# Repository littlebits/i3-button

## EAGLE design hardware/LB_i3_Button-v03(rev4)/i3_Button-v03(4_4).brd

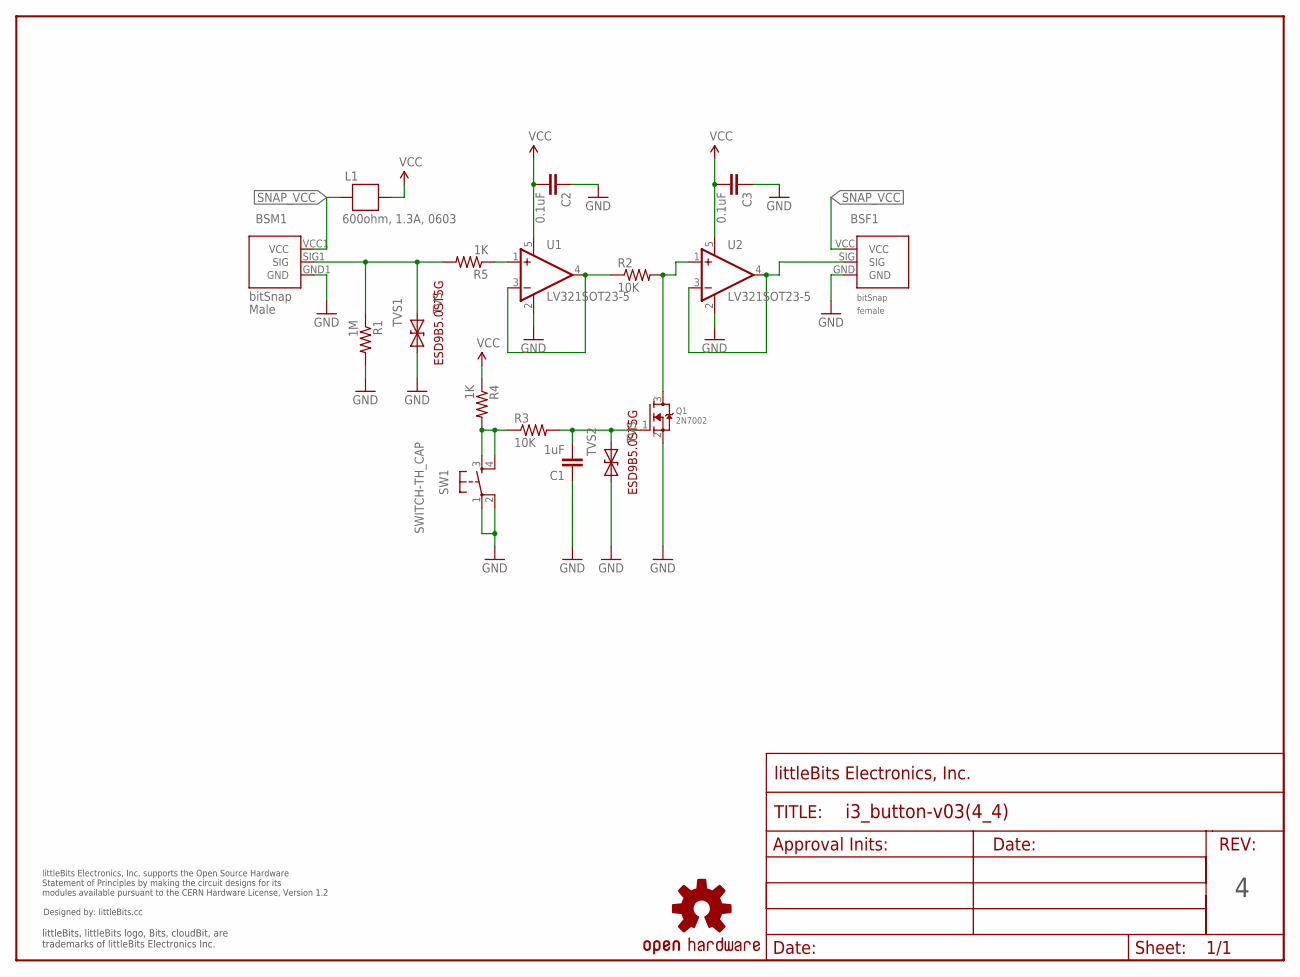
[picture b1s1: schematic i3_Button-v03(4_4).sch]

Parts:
BSF1: BITSNAP_V03_FEMALE
BSM1: BITSNAP_V03_MALE
C1: 1uF; 0603-CAP
C2, C3: 0.1uF; 0603-CAP
FRAME1: FRAME-LETTER-OHWOHW; FABDWG01-OHW
L1: 600ohm, 1.3A, 0603; R0603
Q1: 2N7002; SOT23
R1: 1M; 0603-RES
R2, R3: 10K; 0603-RES
R4, R5: 1K; 0603-RES
SW1: SWITCH-TH_CAP
TVS1, TVS2: TVS; SOD-923
U1, U2: LV321SOT23-5; SOT23-5
U$1: OSHW-LOGOL; OSHW-LOGO-L
U$2: OSHWCREDIT

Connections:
GND: BSF1.GND, BSM1.GND1 (GND), C1.1, C2.1, C3.1, Q1.2 (S), R1.2, SW1.1, SW1.2, TVS1.1 (A), TVS2.1 (A), U1.2 (V-), U2.2 (V-)
unnamed: R2.1, U1.3 (-IN), U1.4 (OUT)
unnamed: BSM1.SIG1 (SIG), R1.1, R5.2, TVS1.2 (C)
unnamed: R5.1, U1.1 (+IN)
unnamed: Q1.3 (D), R2.2, U2.1 (+IN)
unnamed: BSF1.SIG, U2.3 (-IN), U2.4 (OUT)
unnamed: C1.2, Q1.1 (G), R3.2, TVS2.2 (C)
unnamed: R3.1, R4.2, SW1.3, SW1.4
SNAP_VCC: BSF1.VCC, BSM1.VCC1 (VCC), L1.2
VCC: C2.2, C3.2, L1.1, R4.1, U1.5 (V+), U2.5 (V+)

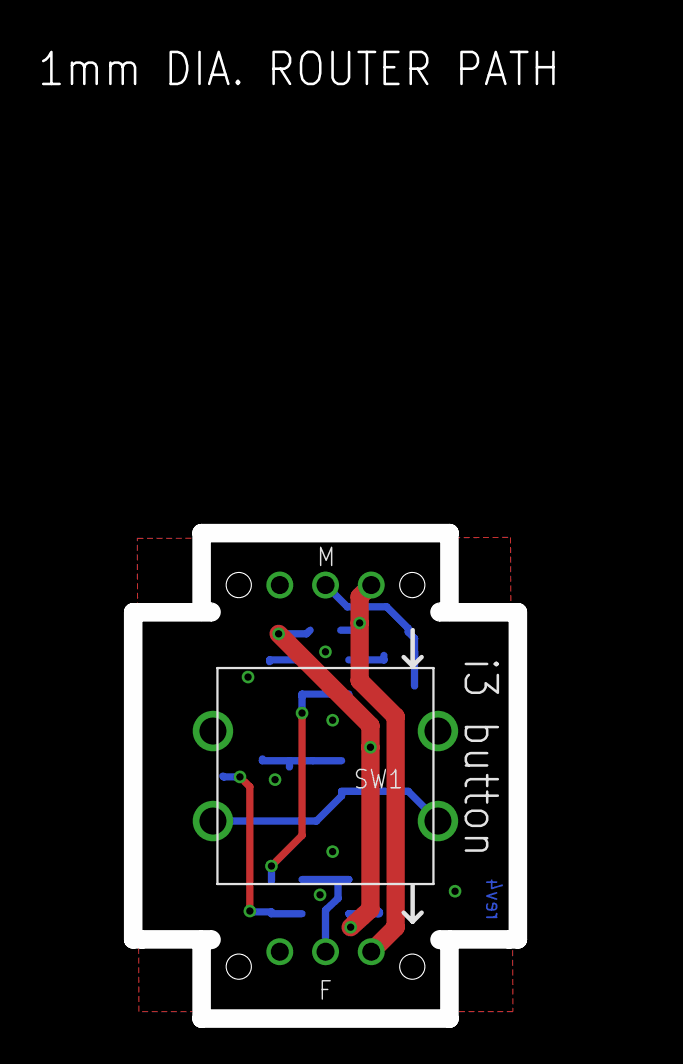
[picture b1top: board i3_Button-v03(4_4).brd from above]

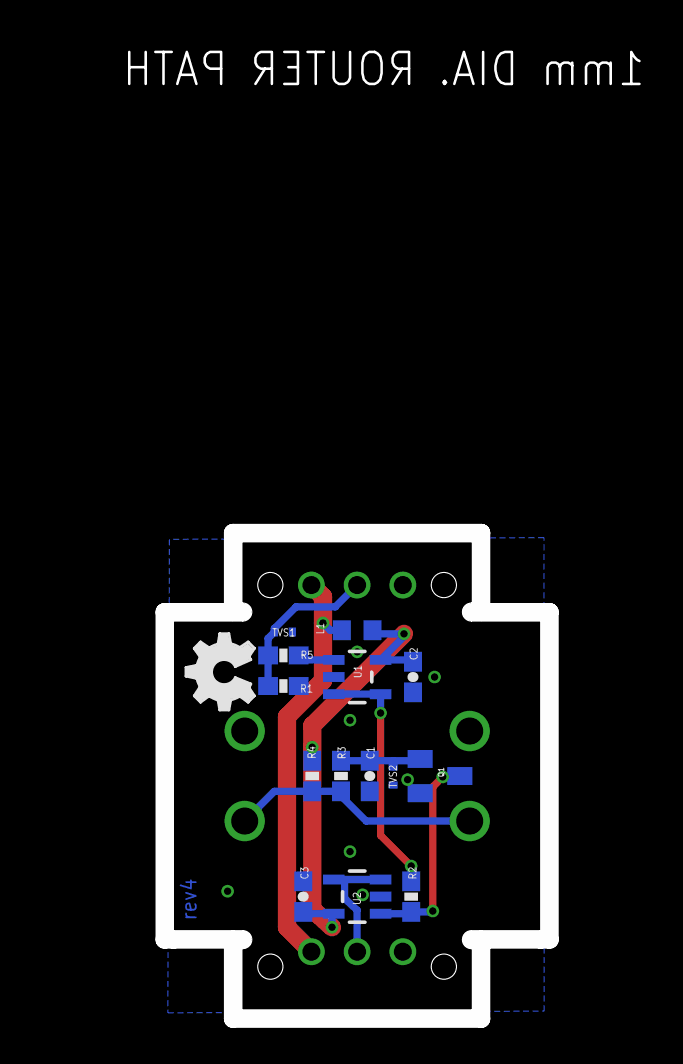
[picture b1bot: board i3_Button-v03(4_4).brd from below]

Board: 2 copper layers, 32.9 x 54.1 mm, 22 parts (14 on the bottom side), 10 nets.

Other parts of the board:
DRILEGEND: DRILEGEND
U$3: OSHW_FILLX150_NOTEXT

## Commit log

2014-11-11 First commit, added hardware files
2014-11-12 Added readme
2016-06-06 add r4-4 HW docs

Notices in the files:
parts and their libraries:
LITTLEBITS: modules available pursuant to the CERN Hardware License,
Version 1.2
LITTLEBITS: modules available pursuant to the CERN Hardware License, Version 1.2
